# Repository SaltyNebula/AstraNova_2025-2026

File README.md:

# AstraNova: UKSEDS National Rocketry Championship 2025-26

**UKC AstraNova** is a student rocketry team from the **University of Kent**, competing in the **UKSEDS National Rocketry Championship (NRC) 2025-26**. This repository is the team's full project record, organised by subsystem; propulsion, structures, recovery, the customer payload, the avionics and rideshare payload, the systems engineering and design reviews, and the supporting documentation. The mission: design, build, and fly a rocket that reaches **670 m**, carries a customer payload alongside the team's own rideshare payload, records its flight data on-board, and recovers safely within **1 km** of the launch site.

> **Flight outcome:** the rocket flew a clean, stable, vertical boost, which validated the aerodynamic and stability design. At apogee it pitched over rather than nosing straight down, so the recovery flight computer's near-freefall deployment condition never triggered and the vehicle came in ballistic. The airframe was lost; the avionics board survived intact. The team took home a UKSEDS **"RUD of the Day"** plaque. The recovery and avionics failures are diagnosed honestly in the [post-mortem](#flight-outcome-and-post-mortem).

## Summary

The vehicle is a 68.9 cm, 769 g cardboard-airframe rocket flying on a **Cesaroni Pro29 108G68-13A** motor (2-grain 29 mm, 107.8 Ns total impulse, ~1.6 s near-constant burn), targeting **670 m (about 2200 ft)**. It carries two payloads: a competition **customer payload (CPD)** powered from the airframe, and the team's own **rideshare payload (the RPD)**. The RPD is a custom flight data logger that records the flight and reports peak altitude on board. Stability sits between *1.75 to 2.5 calibre** throughout ascent, and the final design clears the rail at **19.7 m/s**. Recovery is a nose-cone separation event driven by a flash-paper ejection charge and a **Mercury V1** flight computer on an isolated battery, deploying a 24" Spherachute. The project is documented end to end through the Critical Design Review, Manufacturing Review, and Flight Readiness Review, with a full requirement compliance matrix and mass, power, and financial budgets. The rocket flew, the ascent was stable and straight, and two things then went wrong; both are written up below because the lessons are the real output.

## Key points

- **Mission.** Reach 670 m, carry both payloads, retrieve flight data, and recover within 1 km of the pad, in full compliance with UKSEDS NRC safety rules.
- **Propulsion.** Cesaroni Pro29 108G68-13A; a 2-grain 29 mm motor chosen for its near-constant thrust, giving a steady burn and enough early thrust to clear the rail at speed.
- **Structures.** Cardboard body tube (about 50 mm internal diameter), four lightweight plywood trapezoidal fins, and an ABS-GF (glass-filled ABS) Ogive nose cone with a tight-fitting shoulder; total length 68.9 cm, mass 769 g, validated to hold a 2 kg suspended load without significant deflection.
- **Stability and ascent.** Stability margin held at 2.44 calibres; rail exit at 19.7 m/s; the flight confirmed a stable, vertical boost.
- **Recovery.** Mercury V1 altimeter and flight computer on an independent, isolated battery; flash-paper ejection charge fired by an igniter; nose-cone separation; 24" Spherachute with swivel; Kevlar shock cords over 2 m.
- **Customer payload (CPD).** Powered over a regulated 5 V bus through a keyed XT30 connector from a 4 A buck converter; unpressurised bay for barometric operation; mounted on a removable 3D-printed avionics sled with a bayonet-style twist lock.
- **Rideshare avionics (the RPD).** A from-scratch 2-layer PCB (102 g installed); Raspberry Pi Pico 2 (RP2350), Waveshare 10-DOF IMU (ICM-20948 + BMP280), micro-SD logging, 2.9" e-paper readout, DHT22, buzzer and status LED; barometric altitude at 50 Hz; CSV logging with a Python plotting script; on-board apogee display that holds its value without power; silkscreened team logo.
- **Power.** Shared 7.4 V 2200 mAh 2S Li-ion pack (18650CA-2S-3J, 2.2 A max discharge); a 4 A buck converter feeds the customer payload, an LDO chain feeds the RPD; about 50 minutes of runtime against a combined draw near 1.56 A.
- **Systems and documentation.** CDR, MR, and FRR submissions, a full NRC requirement compliance matrix, and mass, power, and financial budgets all live in this repository.

## Team

University of Kent; supported by the university Physics Society (PhySoc).

| Name | Role | Year / Course |
| --- | --- | --- |
| Cara-Alexandra Hefer | Team Lead / Systems Engineer | 1st / Astronomy, Space Science and Astrophysics |
| Calum Lewis | Vice Team Lead / Avionics Lead | 2nd / Electrical and Electronic Engineering |
| Lucian Willcock | Payload Lead / Avionics | 1st / Physics with Astrophysics |
| Arda Aydinlar | Systems and Structures Engineer | 2nd / Physics with Astrophysics |
| Theodoros Zilios | Recovery / CAD (Propulsion and Recovery) | 1st / Mechanical Engineering |
| Adam McGrath | Recovery Technician | 2nd / Physics |
| Alexander Barry Dee | Propulsion Engineer | 2nd / Physics with Astrophysics |
| Jack Oliver Shorey | Propulsion Engineer | 4th / Physics with Astrophysics |
| Robert Charles Langley Parry | Structural Engineer | 2nd / Ecology and Conservation |

## Subsystems

Each subsystem has its own folder; the highlights and owners are below.

**Systems** (`Systems/`; Cara, Arda). Mission definition, requirement compliance across the MOR, SMN, SAR, ESS, RRS, MIS, CPD, and RPD requirement sets, the mass, power, and financial budgets, and the CDR, MR, and FRR review submissions.

**Propulsion** (`Propulsion/`; Alexander, Jack). Motor selection and characterisation around the Cesaroni Pro29 108G68-13A, thrust-curve analysis, and the rivet-retained 3D-printed motor mount with vibration and compression testing.

**Structures** (`Structures/`; Robert, Arda; CAD by Theodoros). Airframe and fins; a cardboard body tube, four plywood trapezoidal fins chosen for low mass, and an Ogive nose cone, load-tested above 2 kg; OpenRocket model and flight simulation.

**Recovery** (`Recovery/`; Theodoros, Adam; CAD by Theodoros). Nose-cone separation system and nose cone;  ABS-GF nose cone. a flash-paper ejection charge, a Mercury V1 flight computer on an isolated battery, a 24" Spherachute, and Kevlar shock cords, all kept electrically isolated from the rest of the vehicle.

**Payloads** (`CPD/` and `RPD/`; Lucian and Calum on Payloads).The custom flight data logger; PCB design in Fusion 360 Eagle and fabrication at JLCPCB with in-house SMD assembly (`Avionics/`), and the RP2350 firmware and recorder design (`RPD/`), covering the flight-data, apogee-display, and additional-sensor requirements.

**Avionics** (`Avionics/`; Calum and Lucian on Avionics). Overseeing all electronics, including RPD, CPD, and recovery integration and mechanical fit; powering over the regulated 5 V XT30 bus, the unpressurised bay, and the avionics sled and adapter interface. 

## Flight outcome and post-mortem

### What went well

- **Stable, vertical ascent.** The boost was clean and straight, validating the aerodynamic and stability design; the stability margin held in the intended 1.75 to 2.5 calibre band and the vehicle tracked straight off the rail.
- **ABS-GF thermal margin.** The printed parts were made in ABS-GF for its rigidity and heat resistance, since the team was concerned the motor casing might melt nearby plastic. In flight the heat was not an issue at all; the parts came through untouched.
- **Flew on a substitute motor.** The vehicle flew successfully even though it launched on a motor it had not been tuned for (see below), which speaks to margin in the design.

### What went wrong

**Motor substitution.** The motor the team had ordered through UKSEDS was taken before launch, so AstraNova was issued a different motor that the flight had not been calculated or simulated for. The rocket flew regardless, but this changed the expected flight profile.

**Recovery (vehicle level).** Deployment depended on the Mercury V1 detecting a near-freefall, under 1 g condition at apogee. Because the rocket flew so straight on the way up, it carried that momentum over the top and pitched sideways rather than nosing into a clean vertical descent; it never "went straight down." Broadside, aerodynamic load kept the measured acceleration above 1 g, so the deployment window never opened and the rocket came in ballistic. The nose and carbon rods were destroyed on impact. The lesson is direct: a single accelerometer threshold is an unreliable apogee and deploy trigger, because a stable, non-vertical attitude at apogee never produces the expected freefall reading.

**RPD (avionics).** The board powered up, beeped, and wrote its startup calibration row, but logged no flight data. The cause was a **shared-source power brownout**. The 18650CA-2S-3J pack is rated to 2.2 A maximum discharge, and the steady draw (about 1.5 A for the customer payload plus the rideshare) already sat near 1.56 A, leaving very little headroom; the high-dropout regulator chain then gave away most of the voltage margin, and with no bulk capacitance for transient ride-through, the e-paper refresh bursts and the arm-time SD write transient pushed the pack past its limit and dropped the rail below the RP2350 brownout threshold. The board reset mid-arm and only the startup row reached the card.

→ **Full write-up: [Documentation/Avionics_RPD_and_Flight_Postmortem.md](Documentation/Avionics_RPD_and_Flight_Postmortem.md)**

## Quick specs

| Parameter | Value |
| --- | --- |
| Competition | UKSEDS National Rocketry Championship 2025-26 |
| University | University of Kent |
| Target apogee | 670 m (about 2200 ft) |
| Motor | Cesaroni Pro29 108G68-13A (2-grain 29 mm, 107.8 Ns) |
| Airframe | cardboard body tube, four plywood fins, ABS-GF Ogive nose |
| Length / mass | 68.9 cm / 769 g |
| Stability | 2.44 calibres |
| Rail exit speed | 19.7 m/s |
| Recovery | Mercury V1, flash-paper charge, 24" Spherachute |
| Battery | 7.4 V 2200 mAh 2S Li-ion (18650CA-2S-3J, 2.2 A max discharge) |
| Avionics MCU | Raspberry Pi Pico 2 (RP2350) |
| Avionics sensors | ICM-20948, BMP280, DHT22 |
| Avionics readout | 2.9" e-paper, on-board peak altitude |
| RPD mass | 102 g |

## Repository structure

```
Avionics/        avionics battery, power design and sled
RPD/             rideshare flight data logger hardware and electronics (PCB design)
CPD/             customer payload integration and interface
Propulsion/      motor selection and mount
Recovery/        recovery system design, nose cone,
Structures/      airframe, fins, OpenRocket model
Systems/         systems engineering, requirement traceability
Documentation/   design notes and the avionics + flight write-up, design reviews (CDR, MR, FRR)
Figures/         photos and renders used in the README
LICENSE
README.md
```

## License

Released under the MIT License; see [`LICENSE`](LICENSE). If you would rather the documents and figures carry a content licence (for example CC BY 4.0) separately from the code, the repository can be dual-licensed.

## Documentation note

The engineering and conclusions here are the team's own. An AI assistant was used as a writing aid to structure and draft this README and the flight write-up from the team's design reviews and post-flight diagnosis.

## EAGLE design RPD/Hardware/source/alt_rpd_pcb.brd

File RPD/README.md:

# RPD Hardware

The custom 2-layer PCB for the **RPD**, AstraNova's rideshare flight data logger. Designed in **Fusion 360 (Eagle)** and fabricated at **JLCPCB**, with SMD assembly done in-house with engineering lab-tech support. Installed mass is about **102 g** including the sled.

> The flight-day power failure and the board-level fixes are in [`../Documentation/Avionics_RPD_and_Flight_Postmortem.md`](../Documentation/Avionics_RPD_and_Flight_Postmortem.md); see [Known issues](#known-issues-and-planned-fixes).

## Components

| Subsystem | Part | Interface |
| --- | --- | --- |
| MCU | Raspberry Pi Pico 2 (RP2350), SMD-mounted | ; |
| IMU + barometer | Waveshare 10-DOF (ICM-20948 + BMP280) | I2C1 |
| Storage | micro-SD card | SPI0 |
| Display | 2.9" e-paper V2 (296 x 128) | SPI1 |
| Environment | DHT22 | 1-wire |
| Level shifter | CD74HC4050 (Rev V2 only) | ; |
| Indicators | buzzer, green/red status LEDs, ARM / ZERO buttons | GPIO |
| Customer payload supply | 4 A buck converter, 5 V, female XT30 | ; |
| Rideshare supply | LD1117 LDO chain | ; |
| Power in | 2S Li-ion (18650CA-2S-3J, 7.4 V 2200 mAh) | ; |

The PCB carries a **silkscreened team logo** (requirement RPD-005).

## Power architecture

```
2S Li-ion --+-- buck converter (5V, 4A) ----------------- customer payload (XT30)
            |
            +-- LD1117S50 (5V) -- LD1117S33 (3.3V) ------ RPD rail
```

The customer payload and the RPD share only the **battery input terminal**; downstream each has its own regulation. This shared source, combined with the regulator cascade and a lack of bulk decoupling, is what produced the flight-day brownout.

## Board revisions

- **Rev V2(figure 1), flight board.** ENIG finish on black soldermask; includes the CD74HC4050 level-shifter path. This is the board that flew, and it survived the ballistic impact intact.
- **Rev B(alt), test article.** HASL finish; level shifter removed (redundant for all-3.3 V logic) and the SD card wired directly. Built to validate the simplification before committing it to a flight spin.

*Figure 1: PCB Layout*

## Fabrication notes

- 2-layer board, bottom-layer ground plane, hand-routed critical nets (paired I2C, SPI to SD and e-paper, 0.5 to 1 mm power traces).
- JLCPCB standard 2-layer process; confirm design rules before ordering (min trace and clearance 0.127 mm, min via 0.3 mm hole / 0.6 mm annular ring).
- Power section soldered and voltage-checked first, before populating the rest.

*Figure 2: Schematic of PCB(also see schematic in `../RPD/Hardware/schematic.pdf ` )*

## What lives in this folder

```
hardware/
  schematic.pdf          exported schematic
  layout/                board renders and screenshots
  gerbers/               fabrication outputs (Rev V2 ENIG, Rev B HASL)
  bom.csv                bill of materials
  source/                Fusion 360 / Eagle design files (.sch, .brd)
```

Board photos used by the top-level README go in `../figures/` (for example `avionics.jpg`).

## Known issues and planned fixes

The RPD recorded no flight data due to a shared-source brownout. The hardware changes, in order of effect:

1. **Independent battery for the RPD**, decoupled from the customer rail; this alone breaks the failure chain.
2. **Drop the 5 V to 3.3 V cascade** for a single regulator off the pack, to recover the sag margin the high-dropout LD1117 chain gave away.
3. **Add bulk capacitance** at the board input and next to the SD card and e-paper, for transient ride-through.

See the [full write-up](../Documentation/Avionics_RPD_and_Flight_Postmortem.md) for the reasoning.

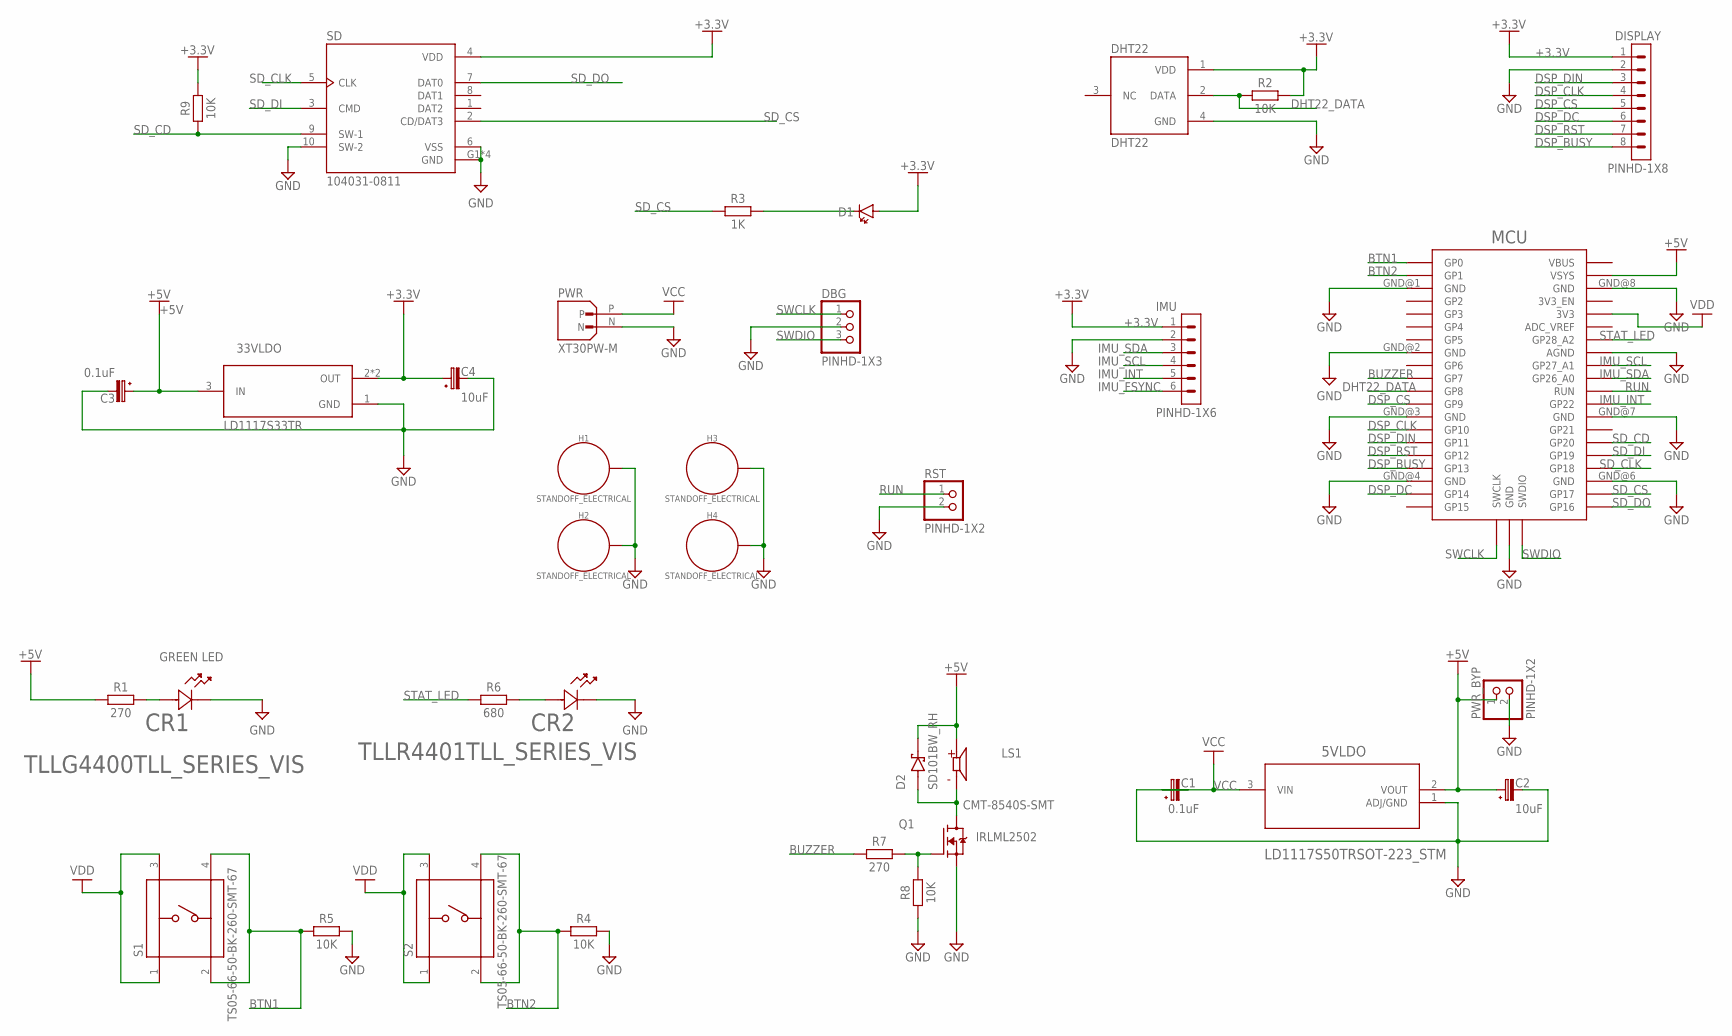
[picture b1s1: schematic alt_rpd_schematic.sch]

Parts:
5VLDO: LD1117S50TRSOT-223_STM; SOT-223_STM
33VLDO: LD1117S33TR; SOT230P700X180-4N
C1, C3: 0.1uF; CAPMP3216X180N
C2, C4: 10uF; CAPMP3216X180N
CR1: TLLG4400TLL_SERIES_VIS; TLL_SERIES_VIS
CR2: TLLR4401TLL_SERIES_VIS; TLL_SERIES_VIS
D1: LED_RED; LEDC2012X110N_FLAT-R
D2: SD101BW_RH; DIO_SD101BW_RH
DBG: PINHD-1X3; 1X03
DHT22: DHT22; XDCR_DHT22
DISPLAY: PINHD-1X8; 1X08
H1, H2, H3, H4: STANDOFF_ELECTRICAL; STANDOFF-ELECTRICAL
IMU: PINHD-1X6; 1X06
LS1: CMT-8540S-SMT; CUI_CMT-8540S-SMT
MCU: RPI_PICO_IG-SMD; RPI_PICO
PWR: XT30PW-M; AMASS_XT30PW-M
PWR_BYP: PINHD-1X2; 1X02
Q1: IRLML2502; SOT95P237X112-3N
R1, R7: 270; RESC3224X71
R2, R4, R5, R8, R9: 10K; RESC3216X70
R3: 1K; RESC3216X70
R6: 680; RESC3224X71
RST: PINHD-1X2; 1X02
S1, S2: TS05-66-50-BK-260-SMT-67; SW_TS05-66-50-BK-260-SMT-67
SD: 104031-0811; MOLEX_104031-0811

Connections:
+3.3V: 33VLDO.2 (OUT), 33VLDO.4 (OUT), C4.1 (+), D1.A, DHT22.1 (VDD), DISPLAY.1, IMU.1, R2.2, R9.2, SD.4 (VDD)
+5V: 5VLDO.2 (VOUT), 33VLDO.3 (IN), C2.1 (+), C3.1 (+), D2.C (K), LS1.P, MCU.VSYS, PWR_BYP.1, R1.1
BTN1: MCU.GP0, R5.1, S1.2, S1.4
BTN2: MCU.GP1, R4.1, S2.2, S2.4
BUZZER: MCU.GP7, R7.1
DHT22_DATA: DHT22.2 (DATA), MCU.GP8, R2.1
DSP_BUSY: DISPLAY.8, MCU.GP13
DSP_CLK: DISPLAY.4, MCU.GP10
DSP_CS: DISPLAY.5, MCU.GP9
DSP_DC: DISPLAY.6, MCU.GP14
DSP_DIN: DISPLAY.3, MCU.GP11
DSP_RST: DISPLAY.7, MCU.GP12
GND: 5VLDO.1 (ADJ/GND), 33VLDO.1 (GND), C1.2 (-), C2.2 (-), C3.2 (-), C4.2 (-), CR1.1, CR2.1, DBG.2, DHT22.4 (GND), DISPLAY.2, H1.P1, H2.P1, H3.P1, H4.P1, IMU.2, MCU.AGND, MCU.GND@1 (GND), MCU.GND@2 (GND), MCU.GND@3 (GND), MCU.GND@4 (GND), MCU.GND@5 (GND), MCU.GND@6 (GND), MCU.GND@7 (GND), MCU.GND@8 (GND), PWR.N, PWR_BYP.2, Q1.2 (S), R4.2, R5.2, R8.1, RST.2, SD.6 (VSS), SD.10 (SW-2), SD.G1 (GND), SD.G2 (GND), SD.G3 (GND), SD.G4 (GND)
IMU_FSYNC: IMU.6
IMU_INT: IMU.5, MCU.GP22
IMU_SCL: IMU.4, MCU.GP27_A1
IMU_SDA: IMU.3, MCU.GP26_A0
unnamed: CR2.2, R6.2
unnamed: CR1.2, R1.2
unnamed: D2.A, LS1.N, Q1.3 (D)
unnamed: Q1.1 (G), R7.2, R8.2
unnamed: D1.C, R3.2
RUN: MCU.RUN, RST.1
SD_CD: MCU.GP20, R9.1, SD.9 (SW-1)
SD_CLK: MCU.GP18, SD.5 (CLK)
SD_CS: MCU.GP17, R3.1, SD.2 (CD/DAT3)
SD_DI: MCU.GP19, SD.3 (CMD)
SD_DO: MCU.GP16, SD.7 (DAT0)
STAT_LED: MCU.GP28_A2, R6.1
SWCLK: DBG.1, MCU.SWCLK
SWDIO: DBG.3, MCU.SWDIO
VCC: 5VLDO.3 (VIN), C1.1 (+), PWR.P
VDD: MCU.3V3, S1.1, S1.3, S2.1, S2.3

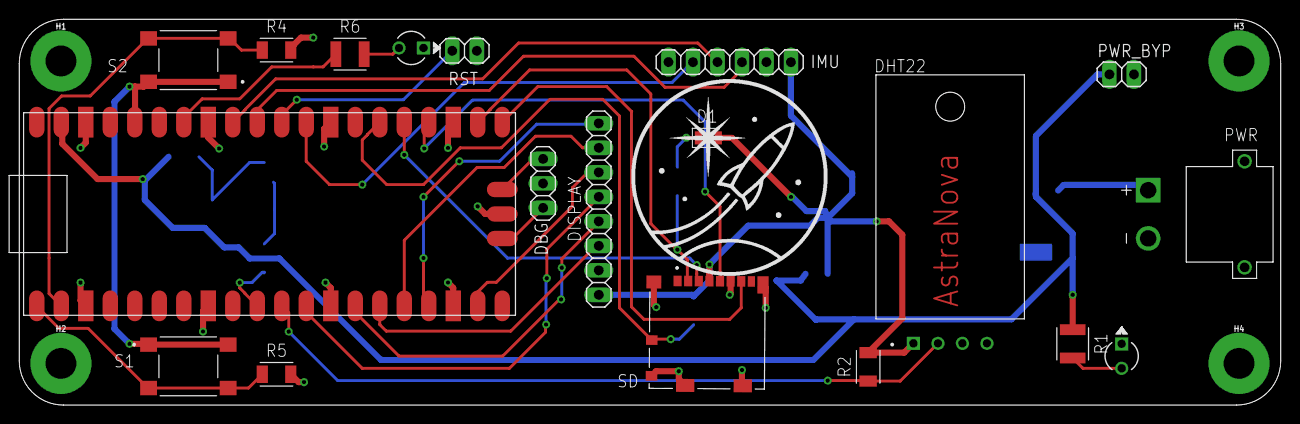
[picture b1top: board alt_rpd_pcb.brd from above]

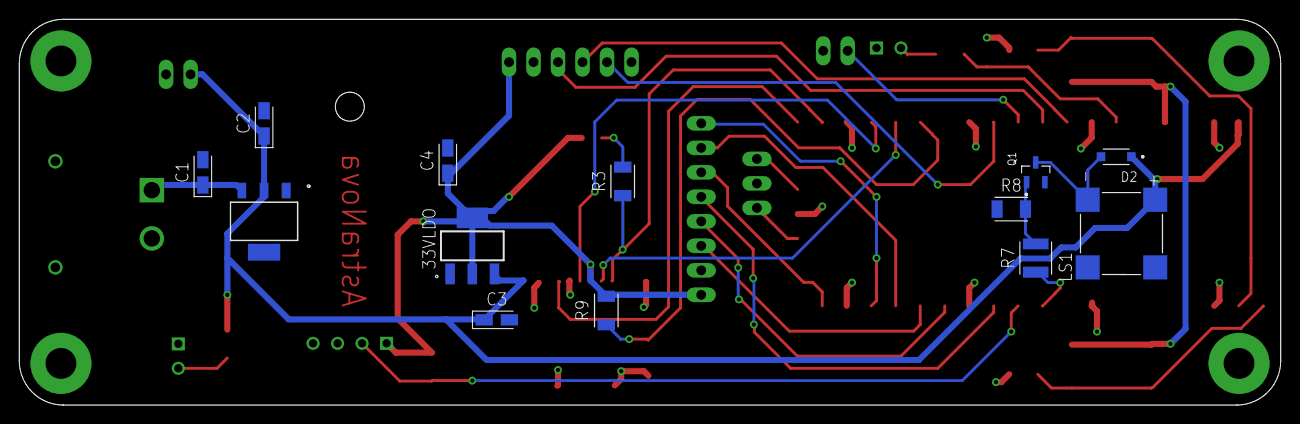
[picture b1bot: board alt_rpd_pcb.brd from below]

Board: 2 copper layers, 130.8 x 40.0 mm, 36 parts (13 on the bottom side), 32 nets.

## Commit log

2026-04-30 Added folders for each division into repo
2026-04-30 added read me under MR
2026-05-06 added Final MR and CDR to their respective folders
2026-05-06 Added Requirement Specifications to repo
2026-05-06 Latest Rocket Design
    Current design on OpenRocket
2026-05-12 FINAL EDITION
    I AM NOT CHANGING THIS!!! IT FITS ALL CRITERIA
2026-05-12 changed nosecone f3d file
2026-05-27 Create scraped
2026-05-28 Added rideshare and test code section to repo
2026-06-04 Add Arduino code for successful squat movement
2026-06-10 Create Payload + avionics launch day instructions
2026-06-10 Rename Notebook 43.pdf to payolad launch day instructions.pdf
2026-06-15 Rename rocket.ork to Final_deisgn_rocket.ork
2026-06-25 moved ork file to structures folder
2026-06-25 renamed rocket mount file names and moved them to structures folder
2026-06-25 Moved structures cad file out of openrocket folder and final open rocket file into open rocket folder
2026-06-25 reanamed payloads folder to CPD and rideshare payloadds folder to RPD
2026-06-25 Deleted test code folder and added full sections to rpd
    The rpd folder now contains a hardware and firmware folder containing cad, pcb and code. in addition a readme has been added and the python file for reading the rpd output
2026-06-25 renamed fins files and moved them to structures folder
2026-06-25 added figures folder to repo
    included team logos
2026-06-25 moved nosecone f3d files from structures to recovery folder
2026-06-25 reorganised cpd folder and added vehicle launch adapter step file
2026-06-25 added rpd casing to rpd folder
2026-06-25 changed names of final chamber in recovery folder and added v1 versions
2026-06-25 added final top motor casing to structures folder
2026-06-25 created avionics folder in repo and added battery holder step file
2026-06-25 added license to repo
2026-06-25 created systems folder and moved requirement specifications to it
2026-06-25 Created propulsion folder and moved all motor related files to it
2026-06-25 movwed cdr and fr folders to documention folder
2026-06-25 renamed f3d files in propulsion for uniformity
2026-06-25 created FRR folder in documentation and added FRR pdf
2026-06-25 Rename NRC-SOW 25_26 - 001 (1).pdf to NRC-SOW 25_26 - 001.pdf
2026-06-25 Rename NRC-RS 25_25 - 002.docx.pdf to NRC-RS 25_25 - 002.pdf
2026-06-25 created feeback folder in documention
    added two feedback pdfs by ukseds inside folder
2026-06-25 added postmortem file in documentation
2026-06-25 Fix link formatting in README.md
2026-06-26 added rpd board schematic and layout images to rpd hardware folder
2026-06-26 added extra images for rocket section to figures folder
2026-06-26 added aftermath rocket pictures to figures folder
2026-06-26 added launch gif and recovery jpg
2026-06-26 added logos to figures directory
2026-06-26 added rocket 3d render to figures
2026-06-26 gave astranova a transparent background
2026-06-26 added UKSEDS NRC logo to figures directory
2026-06-26 added physoc logo to figures
2026-06-26 Revamped README for UKC AstraNova project details
    Expanded the README to include detailed project information, team roles, subsystem descriptions, flight outcomes, and specifications for the UKC AstraNova rocketry project.
2026-06-26 Fix typos and add figures in README
    Corrected typographical errors in board revision descriptions and added figures for clarity.
2026-06-26 rearanged rpd hardware folder
    added layout gerber and source folders and moved original files into their respective folders
2026-06-26 Fix image paths and figure references in README
    Updated image paths in README and corrected figure references.
2026-06-26 Fix typos in board revision descriptions
2026-06-26 Add schematic image to README
    Updated README with schematic image reference.
2026-06-26 moved rocket postmortem image from figures to documentation
2026-06-26 Update avionics postmortem with image
    Added an image to the postmortem documentation and clarified a point about the SD card failure.
2026-06-26 added v2 schematic pdf to rpd layout directory
2026-06-26 Swap images for payload and avionics sections
    Updated image references in the README for payload integration and avionics.
2026-06-26 Revise repository structure descriptions
    Updated descriptions for Avionics, Recovery, and Structures sections.
2026-06-26 added flashpaper test under recovery directory
2026-06-26 added readme file to recovery section
2026-06-26 Fix image link for parachute deployment test
    Updated image reference for parachute deployment test in README.
2026-06-26 moved schematic pdf out of layout section and into general hardware directory and added BOM files
2026-06-26 Fix schematic PDF link in README
    Updated the path to the schematic PDF in the README.
2026-06-27 Update requirement specifications CSV
2026-06-27 Revamped requirement specifications csv
    Updated requirement specifications with revisions and additional details for various components.
2026-06-27 Change title from 'UKC AstraNova' to 'AstraNova'
    Updated project title in README.md for clarity.
2026-06-27 added gitignore file to repo

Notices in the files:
parts and their libraries:
COPYRIGHT: Copyright (C) 2026 Ultra Librarian. All rights reserved.
